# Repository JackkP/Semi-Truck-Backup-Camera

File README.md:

# Semi-Truck-Backup-Camera
Repository for Team 25 Purdue ECE Senior Design Fall 2025 49022 Senior Design Project. This contains all of the code and schematics for the project. Course-related documentation is stored in google.

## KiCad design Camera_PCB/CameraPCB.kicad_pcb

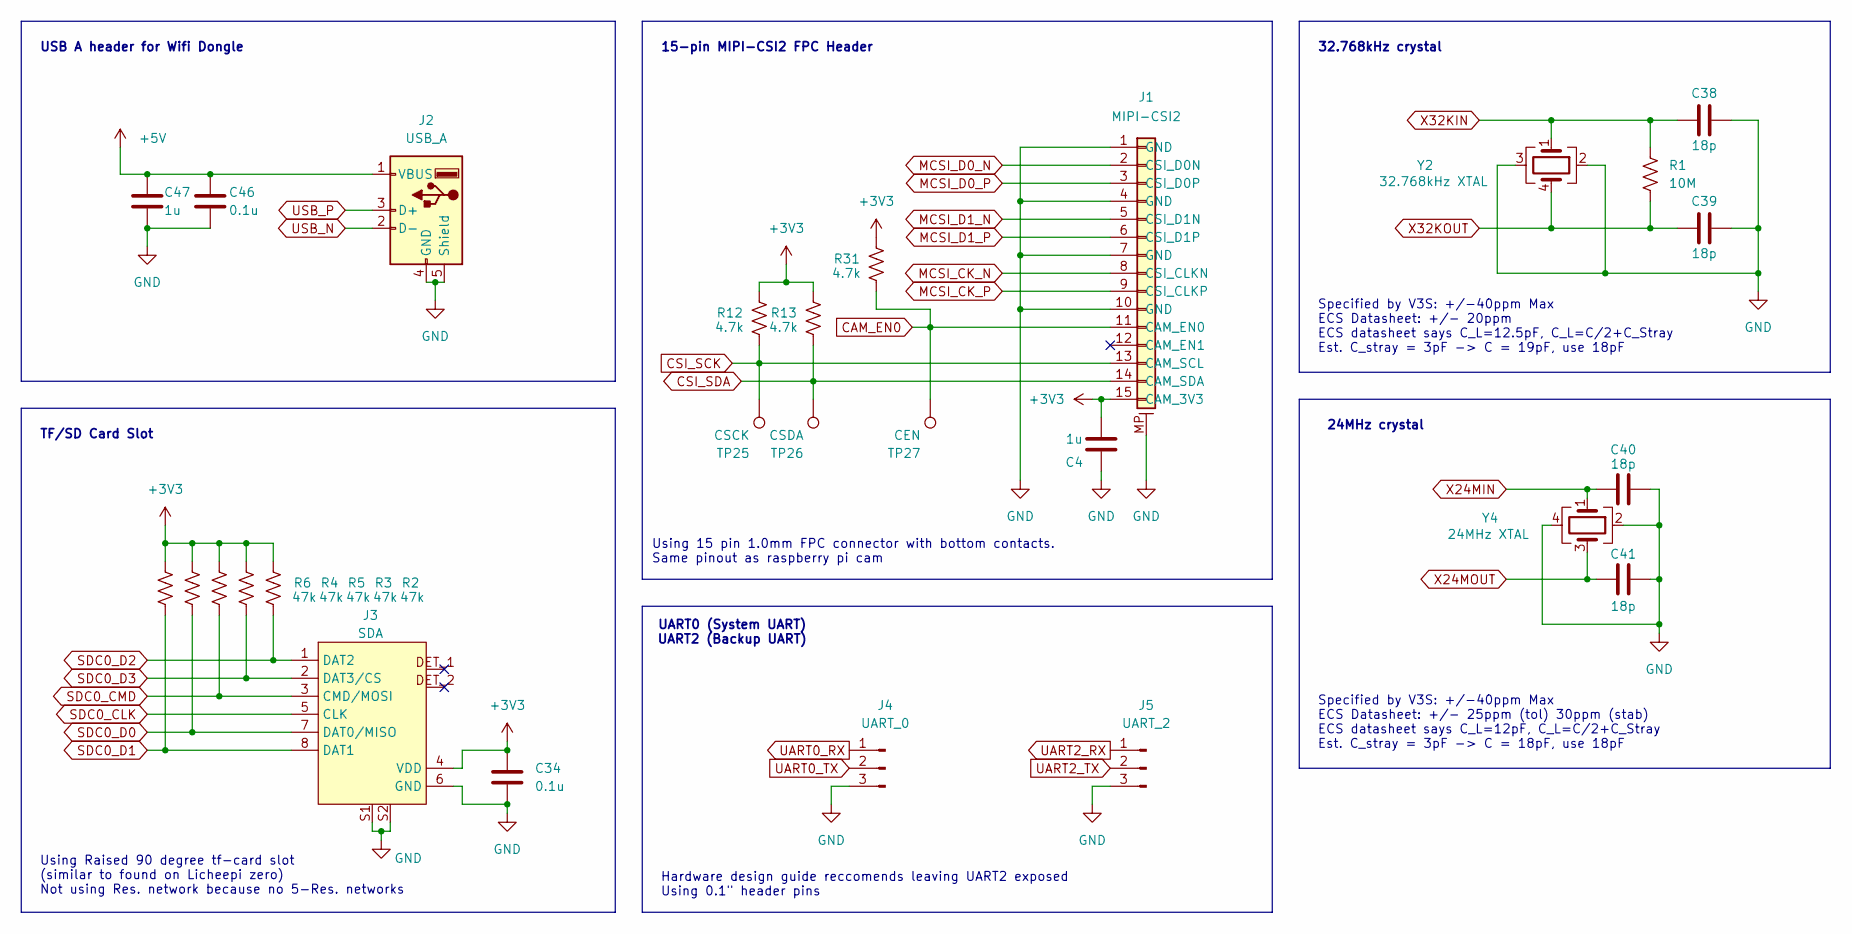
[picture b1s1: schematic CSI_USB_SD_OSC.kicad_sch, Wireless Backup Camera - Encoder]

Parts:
C4, C47: 1u; C_0603_1608Metric_Pad1.08x0.95mm_HandSolder
C34, C46: 0.1u; C_0603_1608Metric_Pad1.08x0.95mm_HandSolder
C38, C39, C40, C41: 18p; C_0603_1608Metric_Pad1.08x0.95mm_HandSolder
J1: MIPI-CSI2; TE_1-84952-5_1x15-1MP_P1.0mm_Horizontal
J2: USB_A; USB_A_Receptacle_GCT_USB1046
J3: SDA; AMPHENOL_10067099-200LF
J4: UART_0; PinHeader_1x03_P2.54mm_Vertical
J5: UART_2; PinHeader_1x03_P2.54mm_Vertical
R1: 10M; R_0603_1608Metric_Pad0.98x0.95mm_HandSolder
R2, R3, R4, R5, R6: 47k; R_0603_1608Metric_Pad0.98x0.95mm_HandSolder
R12, R13, R31: 4.7k; R_0603_1608Metric_Pad0.98x0.95mm_HandSolder
TP25: CSCK; TestPoint_Pad_D1.5mm
TP26: CSDA; TestPoint_Pad_D1.5mm
TP27: CEN; TestPoint_Pad_D1.5mm
Y2: 32.768kHz XTAL; XTAL_ECS-.327-12.5-38-TR
Y4: 24MHz XTAL; XTAL_ECS-240-12-36-AGN-TR

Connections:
+5V: C46.1, C47.1, J2.1 (VBUS); also elsewhere on the board
CAM_EN0: J1.11 (CAM_EN0), R31.2, TP27.1; also elsewhere on the board
CSI_SCK: J1.13 (CAM_SCL), R12.2, TP25.1; also elsewhere on the board
CSI_SDA: J1.14 (CAM_SDA), R13.2, TP26.1; also elsewhere on the board
GND: C4.2, C34.2, C38.2, C39.2, C40.2, C41.1, C46.2, C47.2, J1.1 (GND), J1.4 (GND), J1.7 (GND), J1.10 (GND), J1.MP, J2.4 (GND), J2.5 (Shield), J3.6 (GND), J3.S1, J3.S2, J4.3, J5.3, Y2.2, Y2.3, Y4.2, Y4.4; also elsewhere on the board
HPVCC: C4.1, C34.1, J1.15 (CAM_3V3), J3.4 (VDD), R2.1, R3.1, R4.1, R5.1, R6.1, R12.1, R13.1, R31.1; also elsewhere on the board
MCSI_CK_N: J1.8 (CSI_CLKN); also elsewhere on the board
MCSI_CK_P: J1.9 (CSI_CLKP); also elsewhere on the board
MCSI_D0_N: J1.2 (CSI_D0N); also elsewhere on the board
MCSI_D0_P: J1.3 (CSI_D0P); also elsewhere on the board
MCSI_D1_N: J1.5 (CSI_D1N); also elsewhere on the board
MCSI_D1_P: J1.6 (CSI_D1P); also elsewhere on the board
SDC0_CLK: J3.5 (CLK); also elsewhere on the board
SDC0_CMD: J3.3 (CMD/MOSI), R5.2; also elsewhere on the board
SDC0_D0: J3.7 (DAT0/MISO), R4.2; also elsewhere on the board
SDC0_D1: J3.8 (DAT1), R6.2; also elsewhere on the board
SDC0_D2: J3.1 (DAT2), R2.2; also elsewhere on the board
SDC0_D3: J3.2 (DAT3/CS), R3.2; also elsewhere on the board
UART0_RX: J4.1; also elsewhere on the board
UART0_TX: J4.2; also elsewhere on the board
UART2_RX: J5.1; also elsewhere on the board
UART2_TX: J5.2; also elsewhere on the board
USB_N: J2.2 (D-); also elsewhere on the board
USB_P: J2.3 (D+); also elsewhere on the board
X24MIN: C40.1, Y4.1; also elsewhere on the board
X24MOUT: C41.2, Y4.3; also elsewhere on the board
X32KIN: C38.1, R1.1, Y2.1; also elsewhere on the board
X32KOUT: C39.1, R1.2, Y2.4; also elsewhere on the board

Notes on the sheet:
TF/SD Card Slot
Hardware design guide reccomends leaving UART2 exposed Using 0.1" header pins
15-pin MIPI-CSI2 FPC Header
UART0 (System UART) UART2 (Backup UART)
Specified by V3S: +/-40ppm Max ECS Datasheet: +/- 25ppm (tol) 30ppm (stab) ECS datasheet says C_L=12pF, C_L=C/2+C_Stray Est. C_stray = 3pF -> C = 18pF, use 18pF
Specified by V3S: +/-40ppm Max ECS Datasheet: +/- 20ppm ECS datasheet says C_L=12.5pF, C_L=C/2+C_Stray Est. C_stray = 3pF -> C = 19pF, use 18pF
32.768kHz crystal
Using 15 pin 1.0mm FPC connector with bottom contacts. Same pinout as raspberry pi cam
24MHz crystal
USB A header for Wifi Dongle
Using Raised 90 degree tf-card slot (similar to found on Licheepi zero) Not using Res. network because no 5-Res. networks

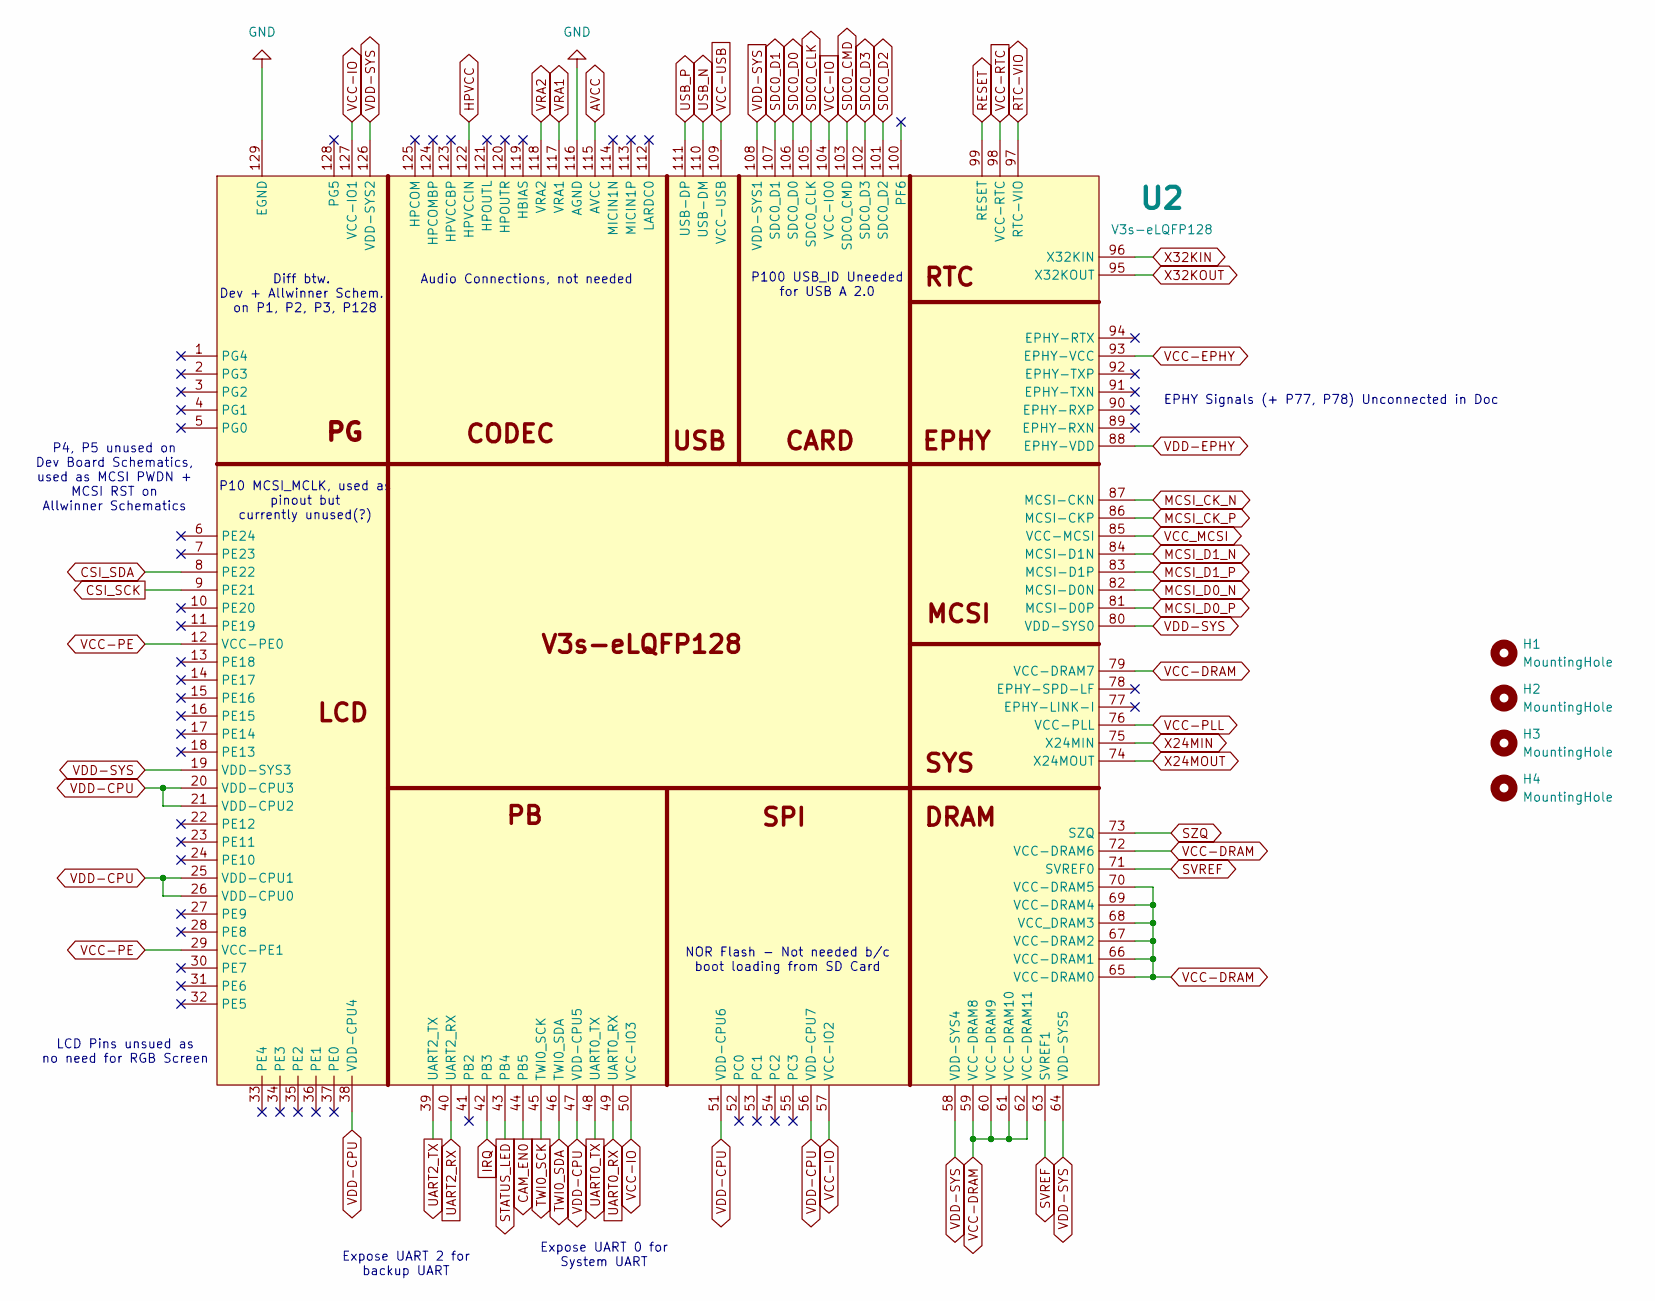
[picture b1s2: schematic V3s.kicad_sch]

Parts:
H1, H2, H3, H4: MountingHole; MountingHole_2.2mm_M2
U2: V3s-eLQFP128; LQFP-128_14x14mm_P0.4mm

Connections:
AVCC: U2.76 (VCC-PLL), U2.115 (AVCC); also elsewhere on the board
CAM_EN0: U2.44 (PB5); also elsewhere on the board
CSI_SCK: U2.9 (PE21); also elsewhere on the board
CSI_SDA: U2.8 (PE22); also elsewhere on the board
GND: U2.116 (AGND), U2.129 (EGND); also elsewhere on the board
HPVCC: U2.12 (VCC-PE0), U2.29 (VCC-PE1), U2.50 (VCC-IO3), U2.57 (VCC-IO2), U2.85 (VCC-MCSI), U2.93 (EPHY-VCC), U2.104 (VCC-IO0), U2.109 (VCC-USB), U2.122 (HPVCCIN), U2.127 (VCC-IO1); also elsewhere on the board
IRQ: U2.42 (PB3); also elsewhere on the board
MCSI_CK_N: U2.87 (MCSI-CKN); also elsewhere on the board
MCSI_CK_P: U2.86 (MCSI-CKP); also elsewhere on the board
MCSI_D0_N: U2.82 (MCSI-D0N); also elsewhere on the board
MCSI_D0_P: U2.81 (MCSI-D0P); also elsewhere on the board
MCSI_D1_N: U2.84 (MCSI-D1N); also elsewhere on the board
MCSI_D1_P: U2.83 (MCSI-D1P); also elsewhere on the board
RESET: U2.99 (RESET); also elsewhere on the board
RTC-VIO: U2.97 (RTC-VIO); also elsewhere on the board
SDC0_CLK: U2.105 (SDC0_CLK); also elsewhere on the board
SDC0_CMD: U2.103 (SDC0_CMD); also elsewhere on the board
SDC0_D0: U2.106 (SDC0_D0); also elsewhere on the board
SDC0_D1: U2.107 (SDC0_D1); also elsewhere on the board
SDC0_D2: U2.101 (SDC0_D2); also elsewhere on the board
SDC0_D3: U2.102 (SDC0_D3); also elsewhere on the board
STATUS_LED: U2.43 (PB4); also elsewhere on the board
SVREF: U2.63 (SVREF1), U2.71 (SVREF0); also elsewhere on the board
SZQ: U2.73 (SZQ); also elsewhere on the board
TWI0_SCK: U2.45 (TWI0_SCK); also elsewhere on the board
TWI0_SDA: U2.46 (TWI0_SDA); also elsewhere on the board
UART0_RX: U2.49 (UART0_RX); also elsewhere on the board
UART0_TX: U2.48 (UART0_TX); also elsewhere on the board
UART2_RX: U2.40 (UART2_RX); also elsewhere on the board
UART2_TX: U2.39 (UART2_TX); also elsewhere on the board
USB_N: U2.110 (USB-DM); also elsewhere on the board
USB_P: U2.111 (USB-DP); also elsewhere on the board
VCC-DRAM: U2.59 (VCC-DRAM8), U2.60 (VCC-DRAM9), U2.61 (VCC-DRAM10), U2.62 (VCC-DRAM11), U2.65 (VCC-DRAM0), U2.66 (VCC-DRAM1), U2.67 (VCC-DRAM2), U2.68 (VCC_DRAM3), U2.69 (VCC-DRAM4), U2.70 (VCC-DRAM5), U2.72 (VCC-DRAM6), U2.79 (VCC-DRAM7); also elsewhere on the board
VCC-RTC: U2.98 (VCC-RTC); also elsewhere on the board
VDD-CPU: U2.19 (VDD-SYS3), U2.20 (VDD-CPU3), U2.21 (VDD-CPU2), U2.25 (VDD-CPU1), U2.26 (VDD-CPU0), U2.38 (VDD-CPU4), U2.47 (VDD-CPU5), U2.51 (VDD-CPU6), U2.56 (VDD-CPU7), U2.58 (VDD-SYS4), U2.64 (VDD-SYS5), U2.80 (VDD-SYS0), U2.88 (EPHY-VDD), U2.108 (VDD-SYS1), U2.126 (VDD-SYS2); also elsewhere on the board
VRA1: U2.117 (VRA1); also elsewhere on the board
VRA2: U2.118 (VRA2); also elsewhere on the board
X24MIN: U2.75 (X24MIN); also elsewhere on the board
X24MOUT: U2.74 (X24MOUT); also elsewhere on the board
X32KIN: U2.96 (X32KIN); also elsewhere on the board
X32KOUT: U2.95 (X32KOUT); also elsewhere on the board

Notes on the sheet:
P10 MCSI_MCLK, used as pinout but currently unused(?)
EPHY Signals (+ P77, P78) Unconnected in Doc
Audio Connections, not needed
NOR Flash - Not needed b/c boot loading from SD Card
P4, P5 unused on Dev Board Schematics, used as MCSI PWDN + MCSI RST on Allwinner Schematics
P100 USB_ID Uneeded for USB A 2.0
Expose UART 2 for backup UART
LCD Pins unsued as no need for RGB Screen
Expose UART 0 for System UART
Diff btw. Dev + Allwinner Schem. on P1, P2, P3, P128

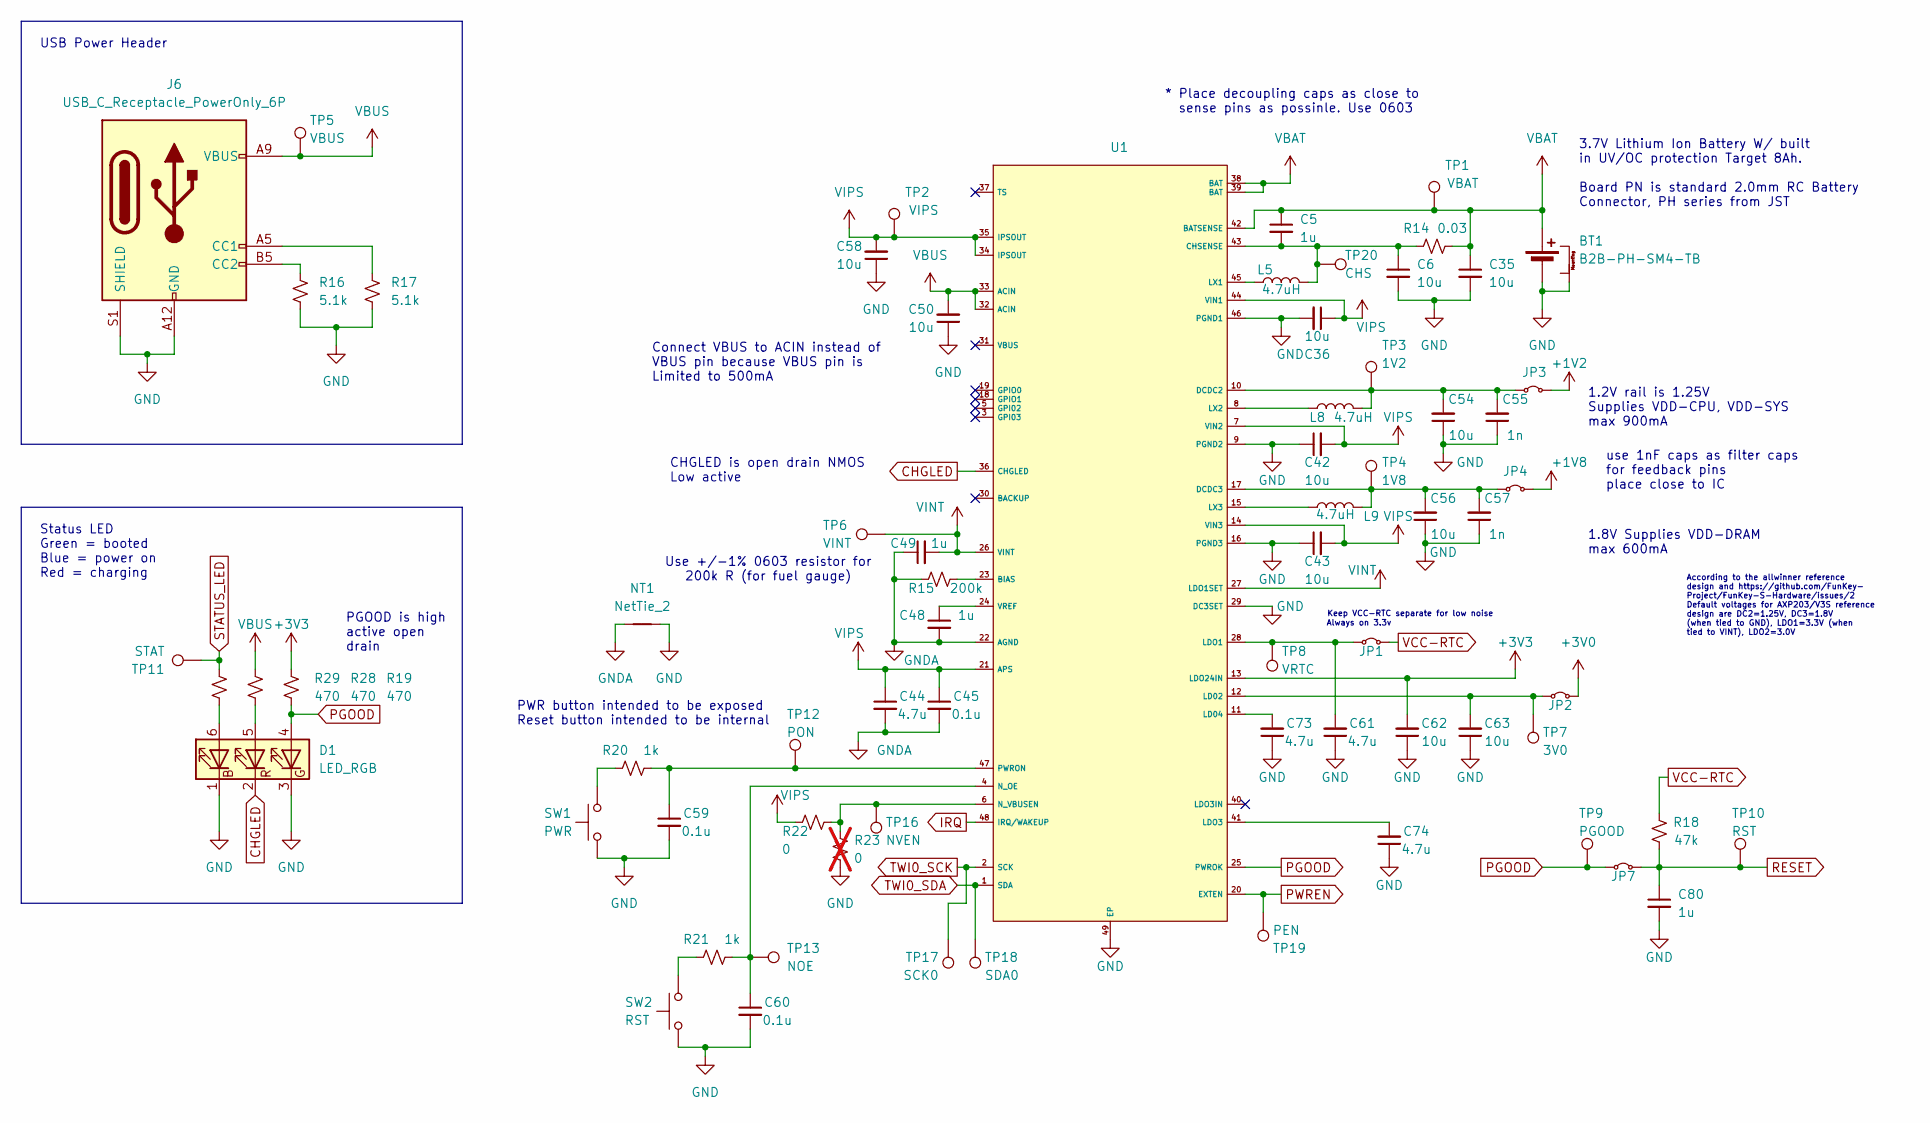
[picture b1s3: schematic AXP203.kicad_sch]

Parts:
BT1: B2B-PH-SM4-TB; JST_PH_B2B-PH-SM4-TB_1x02-1MP_P2.00mm_Vertical
C5, C48, C49, C80: 1u; C_0603_1608Metric_Pad1.08x0.95mm_HandSolder
C6, C35, C36, C42, C43, C50, C54, C56, C58, C62, C63: 10u; C_0805_2012Metric_Pad1.18x1.45mm_HandSolder
C44, C61, C73, C74: 4.7u; C_0805_2012Metric_Pad1.18x1.45mm_HandSolder
C45, C59, C60: 0.1u; C_0603_1608Metric_Pad1.08x0.95mm_HandSolder
C55, C57: 1n; C_0603_1608Metric_Pad1.08x0.95mm_HandSolder
D1: LED_RGB; RGB_LED IN-S66TFT5R5G5B
J6: USB_C_Receptacle_PowerOnly_6P; USB_C_Receptacle_GCT_USB4125-xx-x_6P_TopMnt_Horizontal
JP1, JP2, JP3, JP4, JP7: SolderJumper-2_P1.3mm_Open_Pad1.0x1.5mm
L5, L8, L9: 4.7uH; L_TDK_SLF6045
NT1: NetTie_2; NetTie-2_SMD_Pad0.5mm
R14: 0.03; R_1206_3216Metric
R15: 200k; R_0603_1608Metric_Pad0.98x0.95mm_HandSolder
R16, R17: 5.1k; R_0603_1608Metric_Pad0.98x0.95mm_HandSolder
R18: 47k; R_0603_1608Metric_Pad0.98x0.95mm_HandSolder
R19, R28, R29: 470; R_0603_1608Metric_Pad0.98x0.95mm_HandSolder
R20, R21: 1k; R_0603_1608Metric_Pad0.98x0.95mm_HandSolder
R22: 0; R_0603_1608Metric_Pad0.98x0.95mm_HandSolder
R23: 0; R_0603_1608Metric_Pad0.98x0.95mm_HandSolder; not fitted
SW1: PWR; SW_SPST_PTS647_Sx38
SW2: RST; SW_SPST_PTS647_Sx38
TP1: VBAT; TestPoint_Pad_D1.5mm
TP2: VIPS; TestPoint_Pad_D1.5mm
TP3: 1V2; TestPoint_Pad_D1.5mm
TP4: 1V8; TestPoint_Pad_D1.5mm
TP5: VBUS; TestPoint_Pad_D1.5mm
TP6: VINT; TestPoint_Pad_D1.5mm
TP7: 3V0; TestPoint_Pad_D1.5mm
TP8: VRTC; TestPoint_Pad_D1.5mm
TP9: PGOOD; TestPoint_Pad_D1.5mm
TP10: RST; TestPoint_Pad_D1.5mm
TP11: STAT; TestPoint_Pad_D1.5mm
TP12: PON; TestPoint_Pad_D1.5mm
TP13: NOE; TestPoint_Pad_D1.5mm
TP16: NVEN; TestPoint_Pad_D1.5mm
TP17: SCK0; TestPoint_Pad_D1.5mm
TP18: SDA0; TestPoint_Pad_D1.5mm
TP19: PEN; TestPoint_Pad_D1.5mm
TP20: CHS; TestPoint_Pad_D1.5mm
U1: AXP203; QFN-48-1EP_6x6mm_P0.4mm_EP4.2x4.2mm

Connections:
AVCC: JP2.2 (B); also elsewhere on the board
CHGLED: D1.2 (GK), U1.36 (CHGLED)
GND: BT1.2 (-), BT1.MP, C6.2, C35.2, C36.2, C42.1, C43.1, C50.1, C54.1, C55.1, C56.1, C57.1, C58.1, C59.2, C60.2, C61.1, C62.1, C63.1, C73.1, C74.1, C80.2, D1.1 (RK), D1.3 (BK), J6.A12 (GND), J6.B12 (GND), J6.S1 (SHIELD), NT1.2, R16.2, R17.2, R23.1, SW1.1, SW2.1, U1.9 (PGND2), U1.16 (PGND3), U1.29 (DC3SET), U1.46 (PGND1), U1.49 (EP); also elsewhere on the board
GNDA: C44.2, C45.2, C48.2, C49.1, NT1.1, R15.1, U1.22 (AGND)
HPVCC: C62.2, R19.1, U1.13 (LDO24IN); also elsewhere on the board
IRQ: U1.48 (IRQ/WAKEUP); also elsewhere on the board
unnamed: D1.5 (GA), R28.2
unnamed: D1.6 (RA), R29.2
unnamed: J6.A5 (CC1), R17.1
unnamed: J6.B5 (CC2), R16.1
unnamed: C61.2, JP1.1 (A), TP8.1, U1.28 (LDO1)
unnamed: C63.2, JP2.1 (A), TP7.1, U1.12 (LD02)
unnamed: C54.2, C55.2, JP3.1 (A), L8.2, TP3.1, U1.10 (DCDC2)
unnamed: C56.2, C57.2, JP4.1 (A), L9.2, TP4.1, U1.17 (DCDC3)
unnamed: R20.1, SW1.2
unnamed: R21.1, SW2.2
unnamed: R15.2, U1.23 (BIAS)
unnamed: C5.2, C6.1, L5.2, R14.1, TP20.1, U1.43 (CHSENSE)
unnamed: C73.2, U1.11 (LD04)
unnamed: C74.2, U1.41 (LDO3)
unnamed: L5.1, U1.45 (LX1)
unnamed: L8.1, U1.8 (LX2)
unnamed: L9.1, U1.15 (LX3)
unnamed: C60.1, R21.2, TP13.1, U1.4 (N_OE)
unnamed: R22.2, R23.2, TP16.1, U1.6 (N_VBUSEN)
unnamed: C59.1, R20.2, TP12.1, U1.47 (PWRON)
unnamed: C48.1, U1.24 (VREF)
PGOOD: D1.4 (BA), JP7.1 (A), R19.2, TP9.1, U1.25 (PWROK); also elsewhere on the board
PWREN: TP19.1, U1.20 (EXTEN); also elsewhere on the board
RESET: C80.1, JP7.2 (B), R18.2, TP10.1; also elsewhere on the board
STATUS_LED: R29.1, TP11.1; also elsewhere on the board
TWI0_SCK: TP17.1, U1.2 (SCK); also elsewhere on the board
TWI0_SDA: TP18.1, U1.1 (SDA); also elsewhere on the board
VBAT: BT1.1 (+), C5.1, C35.1, R14.2, TP1.1, U1.38 (BAT), U1.39 (BAT), U1.42 (BATSENSE); also elsewhere on the board
VBUS: C50.2, J6.A9 (VBUS), J6.B9 (VBUS), R28.1, TP5.1, U1.32 (ACIN), U1.33 (ACIN)
VCC-DRAM: JP4.2 (B); also elsewhere on the board
VCC-RTC: JP1.2 (B), R18.1; also elsewhere on the board
VDD-CPU: JP3.2 (B); also elsewhere on the board
VINT: C49.2, TP6.1, U1.26 (VINT), U1.27 (LDO1SET)
VIPS: C36.1, C42.2, C43.2, C44.1, C45.1, C58.2, R22.1, TP2.1, U1.7 (VIN2), U1.14 (VIN3), U1.21 (APS), U1.34 (IPSOUT), U1.35 (IPSOUT), U1.44 (VIN1); also elsewhere on the board

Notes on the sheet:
1.2V rail is 1.25V Supplies VDD-CPU, VDD-SYS max 900mA
PWR button intended to be exposed Reset button intended to be internal
PGOOD is high active open drain
Connect VBUS to ACIN instead of VBUS pin because VBUS pin is Limited to 500mA
USB Power Header
CHGLED is open drain NMOS Low active
use 1nF caps as filter caps for feedback pins place close to IC
According to the allwinner reference design and https://github.com/FunKey- Project/FunKey-S-Hardware/issues/2 Default voltages for AXP203/V3S reference design are DC2=1.25V, DC3=1.8V (when tied to GND), LDO1=3.3V (when tied to VINT), LDO2=3.0V
3.7V Lithium Ion Battery W/ built in UV/OC protection Target 8Ah. Board PN is standard 2.0mm RC Battery Connector, PH series from JST
Always on 3.3v
Keep VCC-RTC separate for low noise
Use +/-1% 0603 resistor for 200k R (for fuel gauge)
Status LED Green = booted Blue = power on Red = charging
* Place decoupling caps as close to sense pins as possinle. Use 0603
1.8V Supplies VDD-DRAM max 600mA

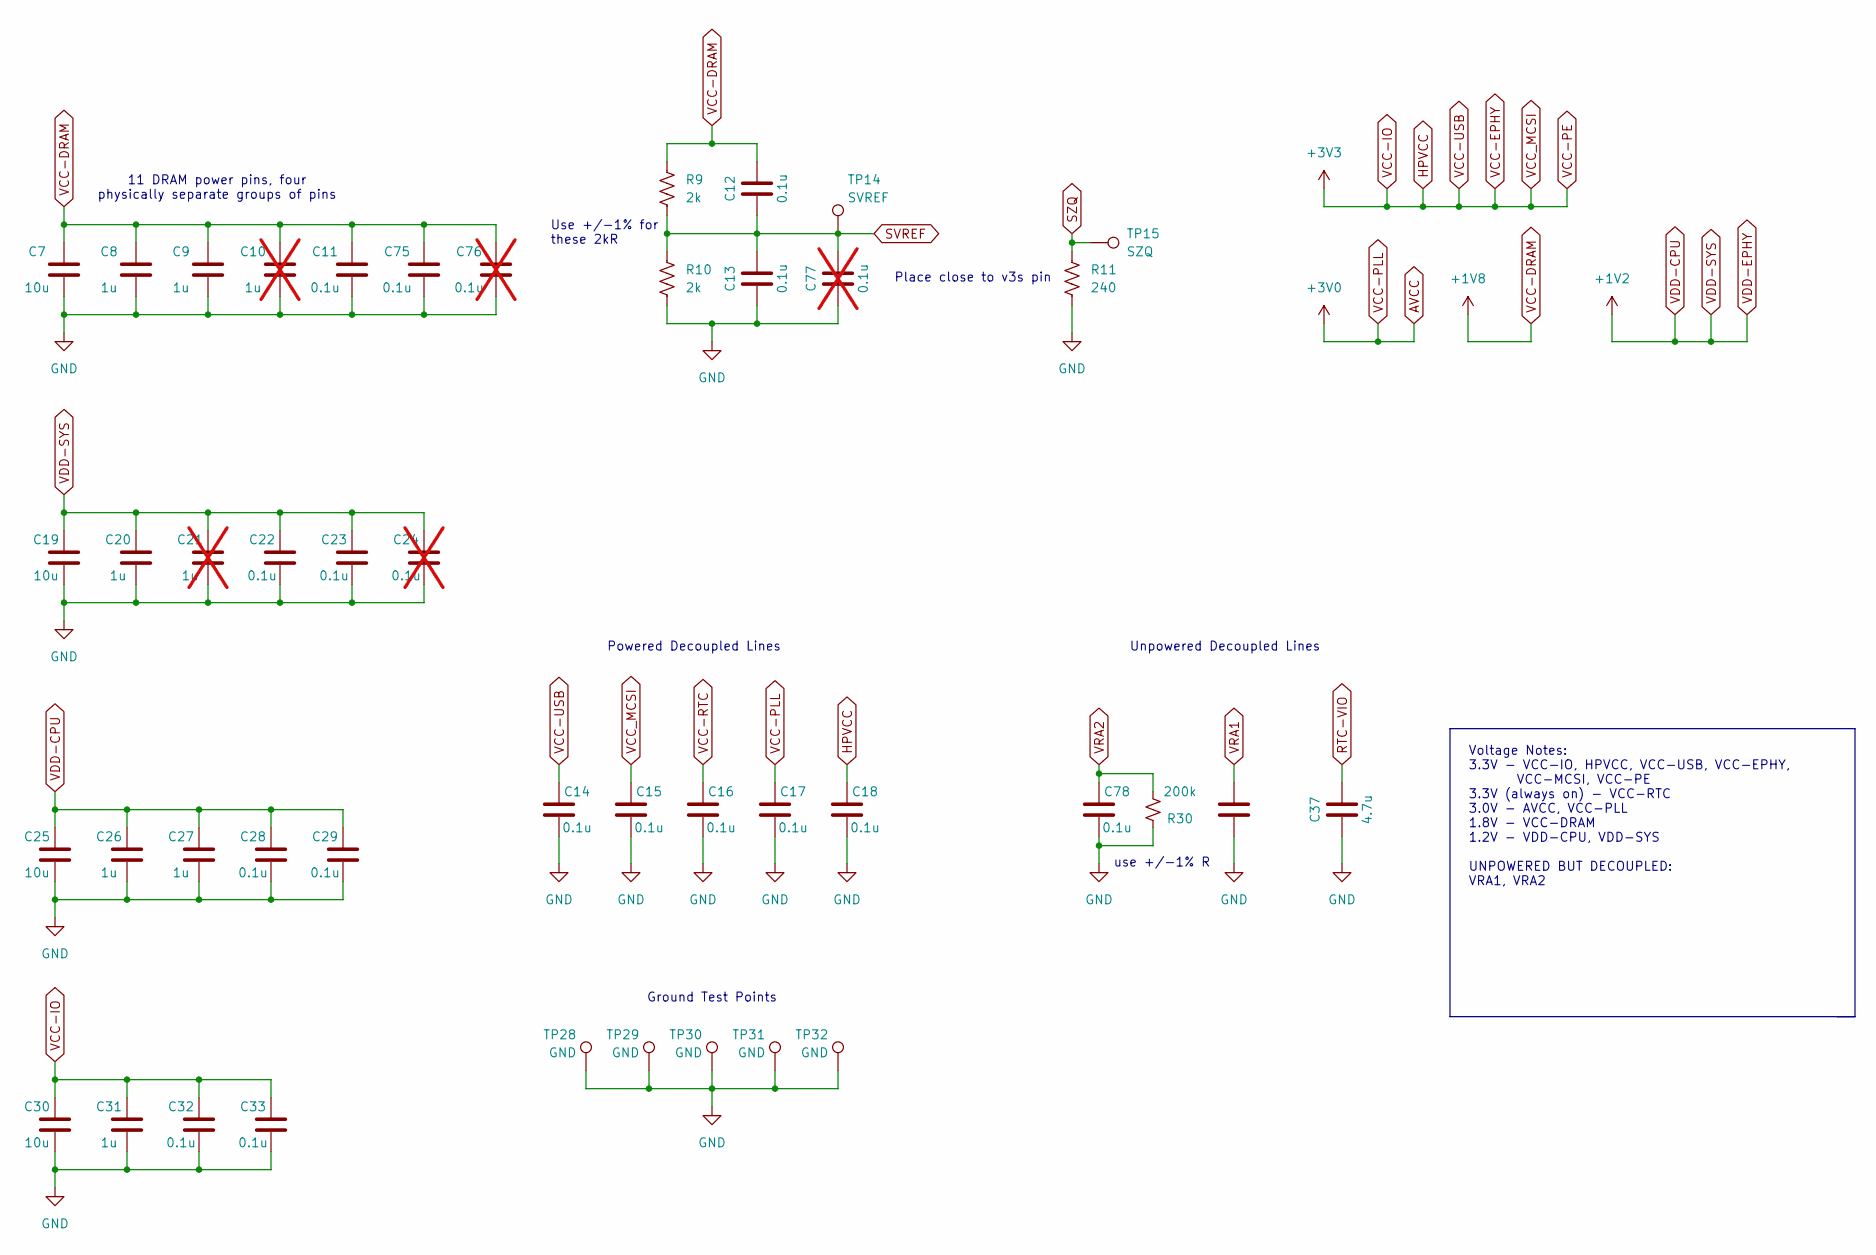
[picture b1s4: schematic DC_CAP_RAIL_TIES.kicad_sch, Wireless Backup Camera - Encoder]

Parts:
C7, C19, C25, C30: 10u; C_0805_2012Metric_Pad1.18x1.45mm_HandSolder
C8, C9, C20, C26, C27, C31: 1u; C_0603_1608Metric_Pad1.08x0.95mm_HandSolder
C10, C21: 1u; C_0603_1608Metric_Pad1.08x0.95mm_HandSolder; not fitted
C11, C12, C13, C14, C15, C16, C17, C18, C22, C23, C28, C29, C32, C33, C75, C78, C79: 0.1u; C_0603_1608Metric_Pad1.08x0.95mm_HandSolder
C24, C76, C77: 0.1u; C_0603_1608Metric_Pad1.08x0.95mm_HandSolder; not fitted
C37: 4.7u; C_0805_2012Metric_Pad1.18x1.45mm_HandSolder
R9, R10: 2k; R_0603_1608Metric_Pad0.98x0.95mm_HandSolder
R11: 240; R_0603_1608Metric_Pad0.98x0.95mm_HandSolder
R30: 200k; R_0603_1608Metric_Pad0.98x0.95mm_HandSolder
TP14: SVREF; TestPoint_Pad_D1.5mm
TP15: SZQ; TestPoint_Pad_D1.5mm
TP28, TP29, TP30, TP31, TP32: GND; TestPoint_Pad_D1.5mm

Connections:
AVCC: C17.2; also elsewhere on the board
GND: C7.1, C8.1, C9.1, C10.1, C11.1, C13.1, C14.1, C15.1, C16.1, C17.1, C18.1, C19.1, C20.1, C21.1, C22.1, C23.1, C24.1, C25.1, C26.1, C27.1, C28.1, C29.1, C30.1, C31.1, C32.1, C33.1, C37.1, C75.1, C76.1, C77.1, C78.1, C79.1, R10.2, R11.2, R30.1, TP28.1, TP29.1, TP30.1, TP31.1, TP32.1; also elsewhere on the board
HPVCC: C14.2, C15.2, C18.2, C30.2, C31.2, C32.2, C33.2; also elsewhere on the board
RTC-VIO: C37.2; also elsewhere on the board
SVREF: C12.1, C13.2, C77.2, R9.2, R10.1, TP14.1; also elsewhere on the board
SZQ: R11.1, TP15.1; also elsewhere on the board
VCC-DRAM: C7.2, C8.2, C9.2, C10.2, C11.2, C12.2, C75.2, C76.2, R9.1; also elsewhere on the board
VCC-RTC: C16.2; also elsewhere on the board
VDD-CPU: C19.2, C20.2, C21.2, C22.2, C23.2, C24.2, C25.2, C26.2, C27.2, C28.2, C29.2; also elsewhere on the board
VRA1: C79.2; also elsewhere on the board
VRA2: C78.2, R30.2; also elsewhere on the board

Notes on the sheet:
Place close to v3s pin
11 DRAM power pins, four physically separate groups of pins
Voltage Notes: 3.3V - VCC-IO, HPVCC, VCC-USB, VCC-EPHY, VCC-MCSI, VCC-PE 3.3V (always on) - VCC-RTC 3.0V - AVCC, VCC-PLL 1.8V - VCC-DRAM 1.2V - VDD-CPU, VDD-SYS UNPOWERED BUT DECOUPLED: VRA1, VRA2
Ground Test Points
Powered Decoupled Lines
Use +/-1% for these 2kR
Unpowered Decoupled Lines
use +/-1% R

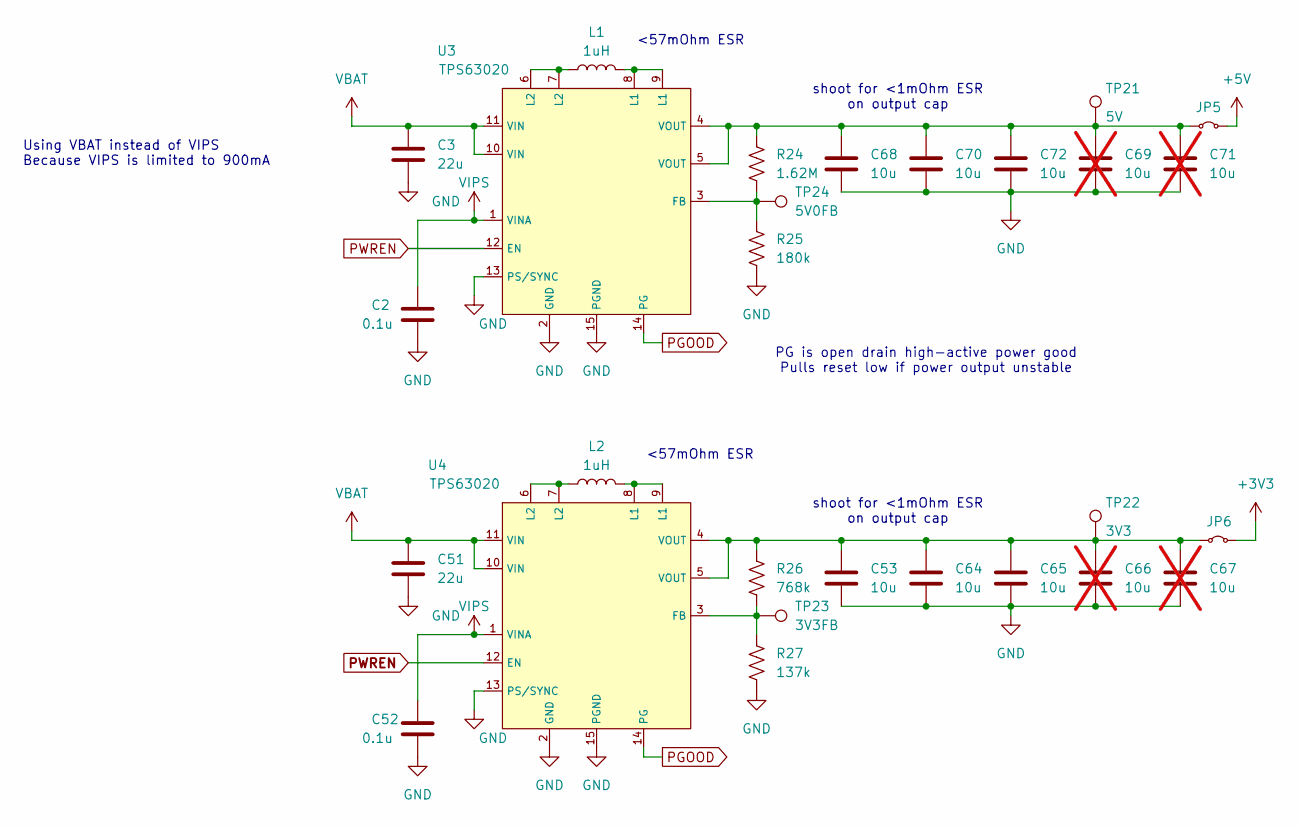
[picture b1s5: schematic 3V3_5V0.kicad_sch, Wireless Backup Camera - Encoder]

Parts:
C2, C52: 0.1u; C_0603_1608Metric_Pad1.08x0.95mm_HandSolder
C3, C51: 22u; C_0805_2012Metric_Pad1.18x1.45mm_HandSolder
C53, C64, C65, C68, C70, C72: 10u; C_0805_2012Metric_Pad1.18x1.45mm_HandSolder
C66, C67, C69, C71: 10u; C_0805_2012Metric_Pad1.18x1.45mm_HandSolder; not fitted
JP5, JP6: SolderJumper-2_P1.3mm_Open_Pad1.0x1.5mm
L1, L2: 1uH; L_Murata_DFE201610P
R24: 1.62M; R_0603_1608Metric_Pad0.98x0.95mm_HandSolder
R25: 180k; R_0603_1608Metric_Pad0.98x0.95mm_HandSolder
R26: 768k; R_0603_1608Metric_Pad0.98x0.95mm_HandSolder
R27: 137k; R_0603_1608Metric_Pad0.98x0.95mm_HandSolder
TP21: 5V; TestPoint_Pad_D1.5mm
TP22: 3V3; TestPoint_Pad_D1.5mm
TP23: 3V3FB; TestPoint_Pad_D1.5mm
TP24: 5V0FB; TestPoint_Pad_D1.5mm
U3, U4: TPS63020; IC_TPS63020DSJT

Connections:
+5V: JP5.2 (B); also elsewhere on the board
GND: C2.2, C3.2, C51.2, C52.2, C53.2, C64.2, C65.2, C66.2, C67.2, C68.2, C69.2, C70.2, C71.2, C72.2, R25.2, R27.2, U3.2 (GND), U3.13 (PS/SYNC), U3.15 (PGND), U4.2 (GND), U4.13 (PS/SYNC), U4.15 (PGND); also elsewhere on the board
HPVCC: JP6.2 (B); also elsewhere on the board
unnamed: C68.1, C69.1, C70.1, C71.1, C72.1, JP5.1 (A), R24.1, TP21.1, U3.4 (VOUT), U3.5 (VOUT)
unnamed: C53.1, C64.1, C65.1, C66.1, C67.1, JP6.1 (A), R26.1, TP22.1, U4.4 (VOUT), U4.5 (VOUT)
unnamed: L1.1, U3.6 (L2), U3.7 (L2)
unnamed: L1.2, U3.8 (L1), U3.9 (L1)
unnamed: L2.1, U4.6 (L2), U4.7 (L2)
unnamed: L2.2, U4.8 (L1), U4.9 (L1)
unnamed: R24.2, R25.1, TP24.1, U3.3 (FB)
unnamed: R26.2, R27.1, TP23.1, U4.3 (FB)
PGOOD: U3.14 (PG), U4.14 (PG); also elsewhere on the board
PWREN: U3.12 (EN), U4.12 (EN); also elsewhere on the board
VBAT: C3.1, C51.1, U3.10 (VIN), U3.11 (VIN), U4.10 (VIN), U4.11 (VIN); also elsewhere on the board
VIPS: C2.1, C52.1, U3.1 (VINA), U4.1 (VINA); also elsewhere on the board

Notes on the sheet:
Using VBAT instead of VIPS Because VIPS is limited to 900mA
shoot for <1mOhm ESR on output cap
<57mOhm ESR
PG is open drain high-active power good Pulls reset low if power output unstable

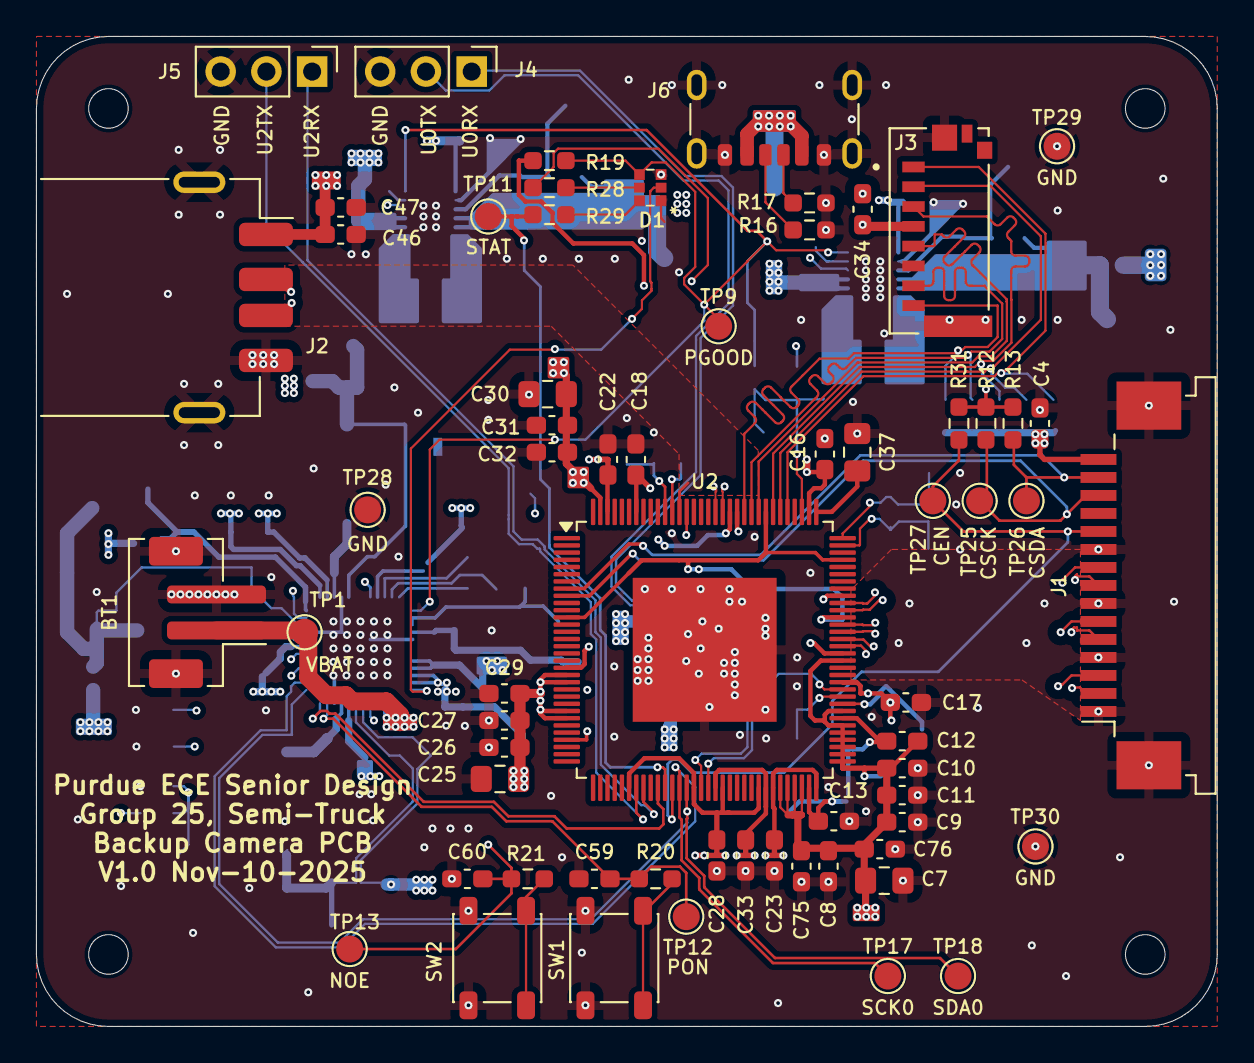
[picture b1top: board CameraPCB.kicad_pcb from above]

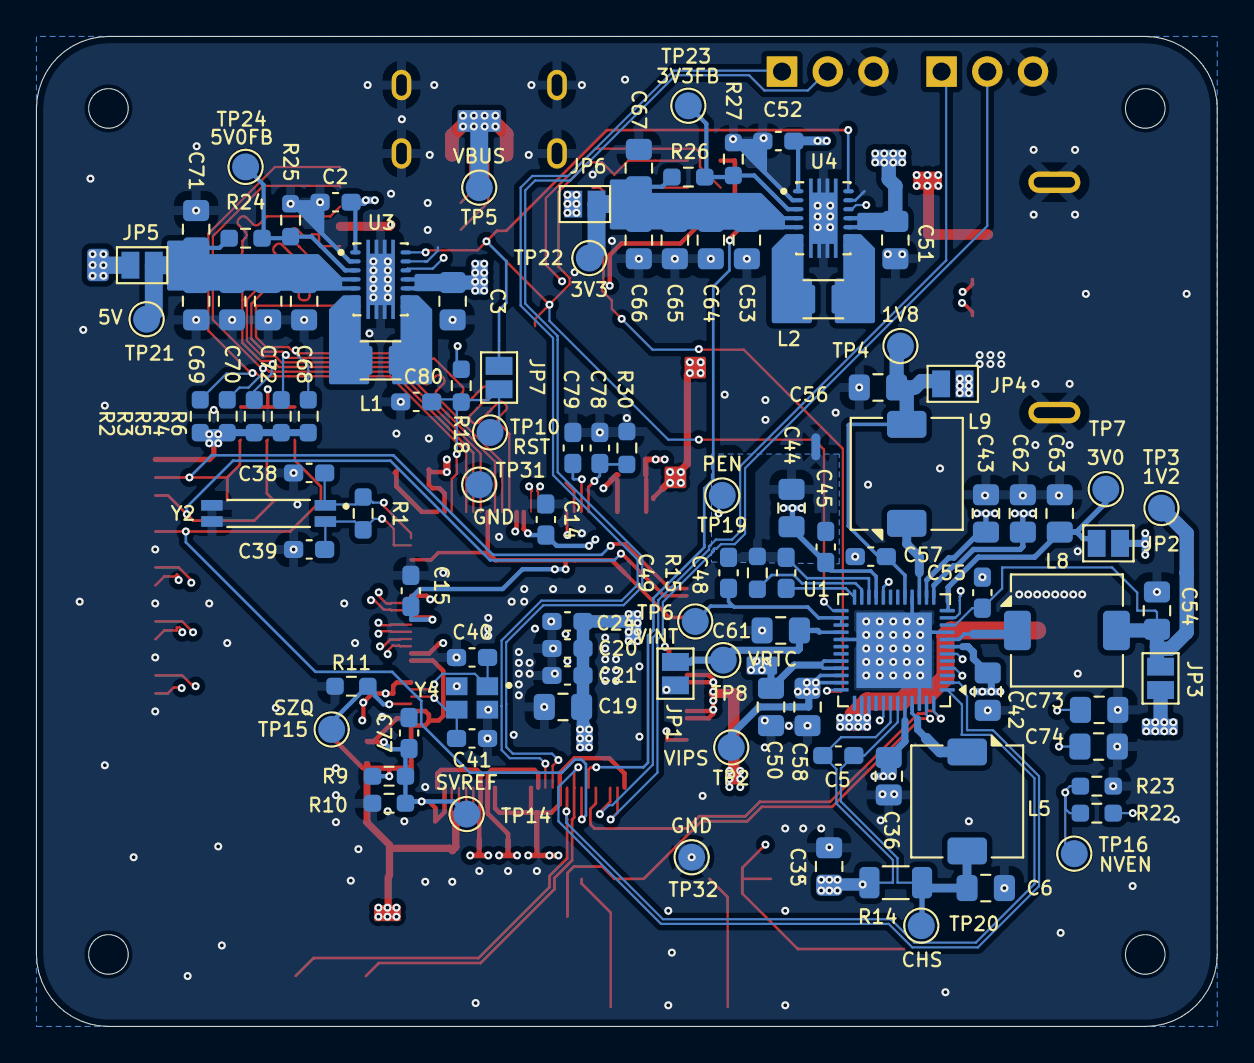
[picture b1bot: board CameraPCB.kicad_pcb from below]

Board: 6 copper layers, 65.6 x 55.0 mm, 173 parts (105 on the bottom side), 79 nets.
